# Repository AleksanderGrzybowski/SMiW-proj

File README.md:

# SMiW-proj
An ATmega16 based clock on steroids

This is DS1307 + ATmega based digital clock, made for Embedded Systems course. Developed on mega16 at the university (cause everyone were using mega8 for no reason), switched to mega8 later.
Includes multiplexing, I2C interfacing and buttons for setting time, brightness and other settings.

In the second version I remade it to work fully on a single 18650 battery (lasts for a week or so on a cheap cell extracted from a broken powerbank), with battery voltage monitoring. USB charger module and boost module (3.7 -> 5) are glued on the backside.

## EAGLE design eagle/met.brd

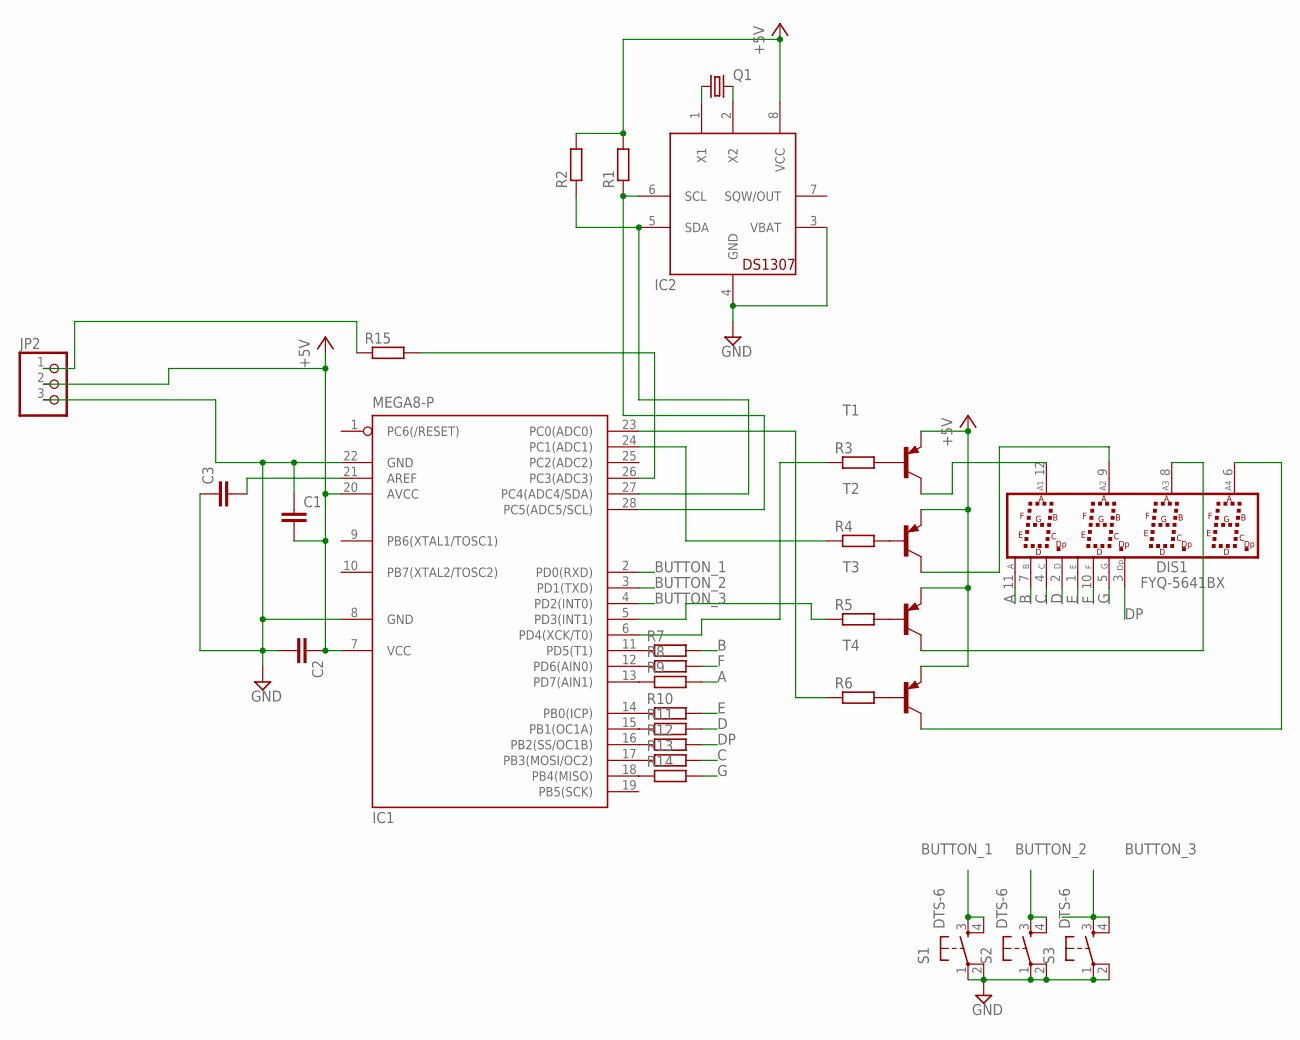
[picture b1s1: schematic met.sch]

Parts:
C1, C2, C3: C-EU025-024X044; C025-024X044
DIS1: FYQ-5641BX; FYQ5641
IC1: MEGA8-P; DIL28-3
IC2: DS1307; DIL08
JP2: PINHD-1X3; 1X03
Q1: CRYSTALTC26V; TC26V
R1, R2: R-EU_0207/2V; 0207/2V
R3, R4, R5, R6, R7, R8, R9, R10, R11, R12, R13, R14, R15: R-EU_0204/2V; 0204V
S1, S2, S3: DTS-6
T1, T2, T3, T4: BC327-PNP-TO92-EBC; TO92-EBC

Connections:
+5V: C1.2, C2.1, IC1.7 (VCC), IC1.20 (AVCC), IC2.8 (VCC), JP2.2, R1.2, R2.2, T1.E, T2.E, T3.E, T4.E
A: DIS1.11 (A), R9.2
B: DIS1.7 (B), R7.2
BUTTON_1: IC1.2 (PD0(RXD)), S1.3, S1.4
BUTTON_2: IC1.3 (PD1(TXD)), S2.3, S2.4
BUTTON_3: IC1.4 (PD2(INT0)), S3.3, S3.4
C: DIS1.4 (C), R13.2
D: DIS1.2 (D), R11.2
D2: DIS1.9 (A2), T2.C
D3: DIS1.8 (A3), T3.C
DOT: IC1.27 (PC4(ADC4/SDA)), IC2.5 (SDA), R2.1
DP: DIS1.3 (DP), R12.2
E: DIS1.1 (E), R10.2
F: DIS1.10 (F), R8.2
G: DIS1.5 (G), R14.2
GND: C1.1, C2.2, C3.1, IC1.8 (GND), IC1.22 (GND), IC2.3 (VBAT), IC2.4 (GND), JP2.3, S1.1, S1.2, S2.1, S2.2, S3.1, S3.2
unnamed: IC2.1 (X1), Q1.1
unnamed: IC2.2 (X2), Q1.2
unnamed: C3.2, IC1.21 (AREF)
unnamed: JP2.1, R15.1
unnamed: DIS1.6 (A4), T4.C
unnamed: IC1.28 (PC5(ADC5/SCL)), IC2.6 (SCL), R1.1
unnamed: IC1.23 (PC0(ADC0)), R6.1
unnamed: IC1.6 (PD4(XCK/T0)), R3.1
unnamed: R5.2, T3.B
unnamed: R3.2, T1.B
unnamed: R4.2, T2.B
unnamed: R6.2, T4.B
unnamed: IC1.24 (PC1(ADC1)), R4.1
unnamed: IC1.5 (PD3(INT1)), R5.1
unnamed: IC1.11 (PD5(T1)), R7.1
unnamed: IC1.12 (PD6(AIN0)), R8.1
unnamed: IC1.13 (PD7(AIN1)), R9.1
unnamed: IC1.14 (PB0(ICP)), R10.1
unnamed: IC1.15 (PB1(OC1A)), R11.1
unnamed: IC1.16 (PB2(SS/OC1B)), R12.1
unnamed: IC1.17 (PB3(MOSI/OC2)), R13.1
unnamed: DIS1.12 (A1), T1.C
unnamed: IC1.18 (PB4(MISO)), R14.1
unnamed: IC1.26 (PC3(ADC3)), R15.2

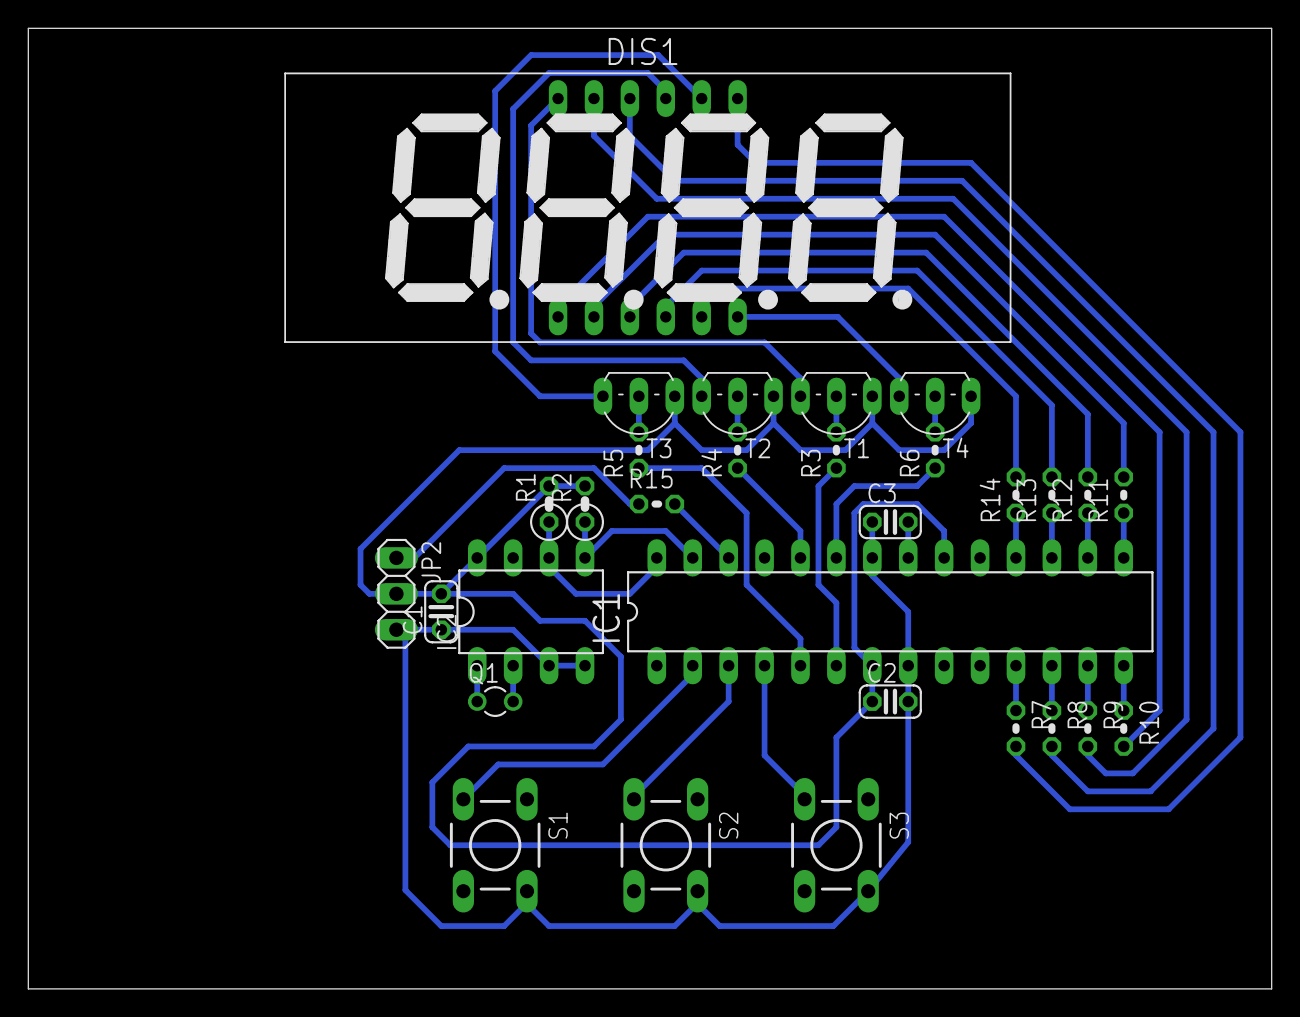
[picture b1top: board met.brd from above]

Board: 2 copper layers, 87.9 x 67.9 mm, 30 parts (0 on the bottom side), 40 nets.

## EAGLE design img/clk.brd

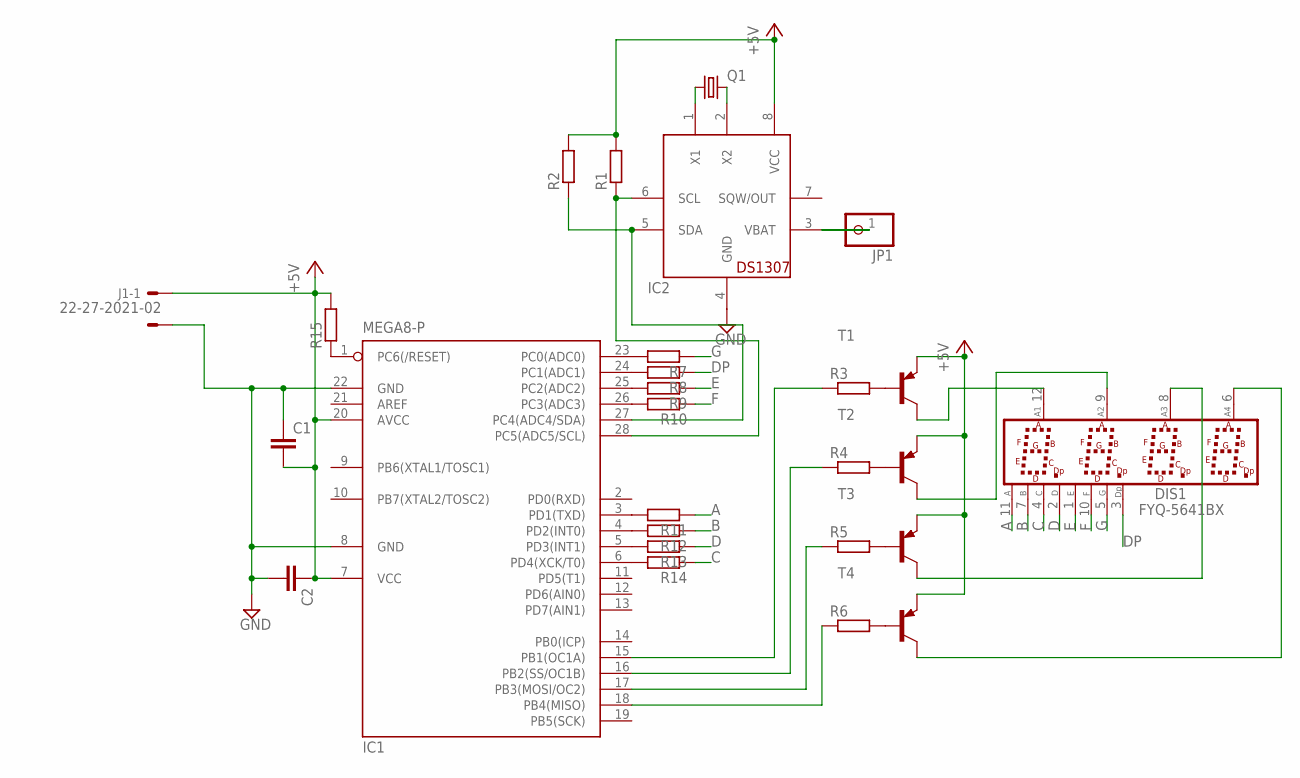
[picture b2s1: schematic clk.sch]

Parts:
C1, C2: C-EU025-024X044; C025-024X044
DIS1: FYQ-5641BX; FYQ5641
IC1: MEGA8-P; DIL28-3
IC2: DS1307; DIL08
J1: 22-27-2021-02; 6410-02
JP1: PINHD-1X1; 1X01
Q1: CRYSTALTC26V; TC26V
R1, R2, R7, R8, R9, R10, R11, R12, R13, R14: R-EU_0207/2V; 0207/2V
R3, R4, R5, R6, R15: R-EU_0204/2V; 0204V
T1, T2, T3, T4: BC327-PNP-TO92-EBC; TO92-EBC

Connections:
+5V: C1.2, C2.1, IC1.7 (VCC), IC1.20 (AVCC), IC2.8 (VCC), J1.1, R1.2, R2.2, R15.2, T1.E, T2.E, T3.E, T4.E
A: DIS1.11 (A), R11.1
B: DIS1.7 (B), R12.1
C: DIS1.4 (C), R14.1
D: DIS1.2 (D), R13.1
D2: DIS1.9 (A2), T2.C
D3: DIS1.8 (A3), T3.C
DOT: IC1.27 (PC4(ADC4/SDA)), IC2.5 (SDA), R2.1
DP: DIS1.3 (DP), R8.1
E: DIS1.1 (E), R9.1
F: DIS1.10 (F), R10.1
G: DIS1.5 (G), R7.1
GND: C1.1, C2.2, IC1.8 (GND), IC1.22 (GND), IC2.4 (GND), J1.2
unnamed: IC2.1 (X1), Q1.1
unnamed: IC2.2 (X2), Q1.2
unnamed: IC1.23 (PC0(ADC0)), R7.2
unnamed: IC1.24 (PC1(ADC1)), R8.2
unnamed: DIS1.6 (A4), T4.C
unnamed: IC1.28 (PC5(ADC5/SCL)), IC2.6 (SCL), R1.1
unnamed: IC2.3 (VBAT), JP1.1
unnamed: IC1.25 (PC2(ADC2)), R9.2
unnamed: R5.2, T3.B
unnamed: R3.2, T1.B
unnamed: R4.2, T2.B
unnamed: R6.2, T4.B
unnamed: IC1.1 (PC6(/RESET)), R15.1
unnamed: IC1.16 (PB2(SS/OC1B)), R4.1
unnamed: IC1.17 (PB3(MOSI/OC2)), R5.1
unnamed: IC1.18 (PB4(MISO)), R6.1
unnamed: IC1.26 (PC3(ADC3)), R10.2
unnamed: IC1.3 (PD1(TXD)), R11.2
unnamed: IC1.4 (PD2(INT0)), R12.2
unnamed: IC1.5 (PD3(INT1)), R13.2
unnamed: IC1.6 (PD4(XCK/T0)), R14.2
unnamed: IC1.15 (PB1(OC1A)), R3.1
unnamed: DIS1.12 (A1), T1.C

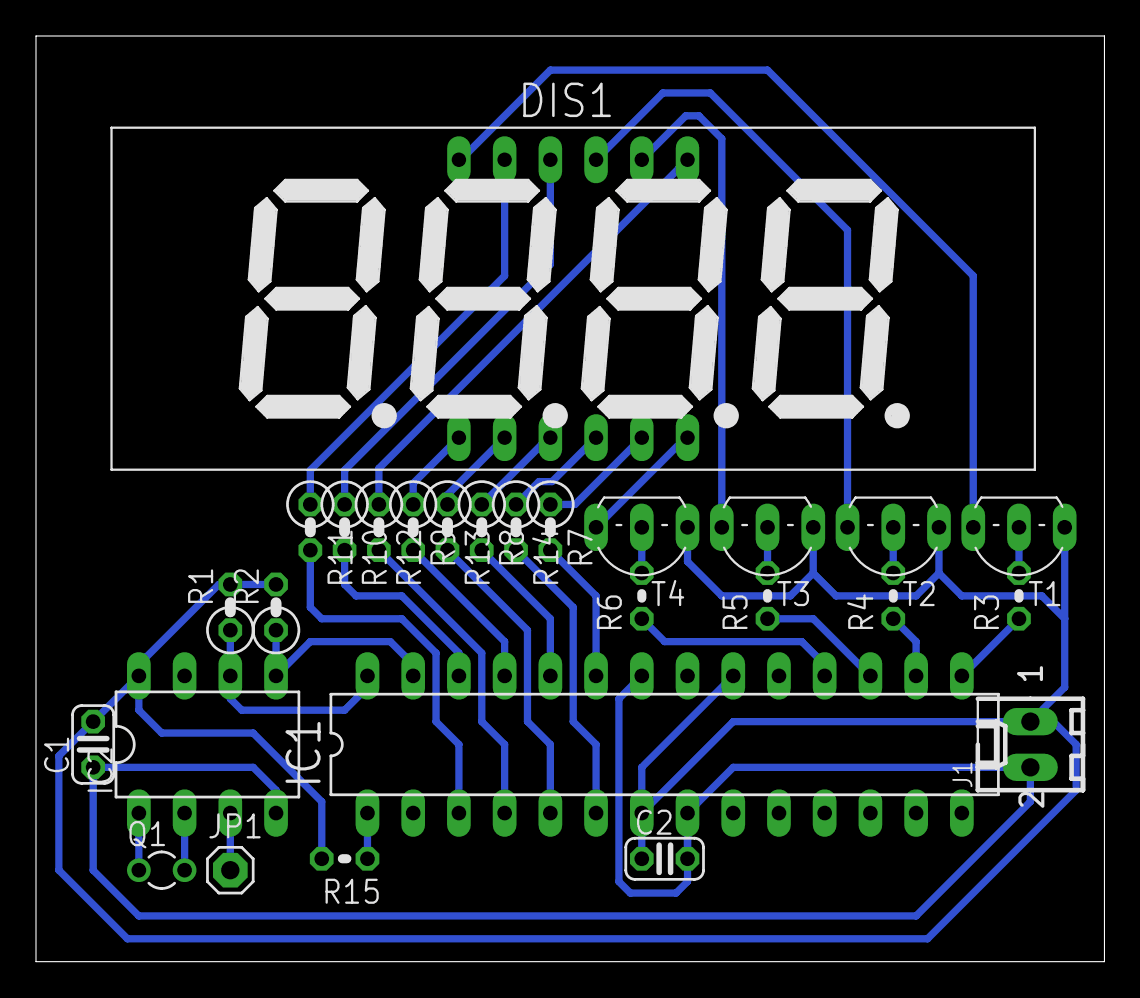
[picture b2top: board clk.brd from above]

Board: 2 copper layers, 59.4 x 51.4 mm, 27 parts (0 on the bottom side), 36 nets.

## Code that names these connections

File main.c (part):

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
/////////////////////////////////////////////////////

#define DOT 128
#define G 64
#define F 32
#define E 16
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    }

    /* prevent ghosting */
    PORTB |= (1 << PB0) | (1 << PB1) | (1 << PB2) | (1 << PB3) | (1 << PB4);
    PORTD |= (1 << PD5) | (1 << PD6) | (1 << PD7);

    PORTC |= (1 << PC0) | (1 << PC1);
    PORTD |= (1 << PD3) | (1 << PD4);

    /* turn on/off current digit, based on pwm current value */
    int real_brightness = is_night ? NIGHT_BRIGHTNESS : brightness;
    if (pwm_iter < real_brightness) {
        if (current_digit == 3) {
            PORTC &= ~(1 << PC0);
        }
        if (current_digit == 1) {
            PORTC &= ~(1 << PC1);
        }
        if (current_digit == 2) {
            PORTD &= ~(1 << PD3);
        }
        if (current_digit == 0) {
            PORTD &= ~(1 << PD4);
        }
    } 

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    uint8_t value = ~tab[display[current_digit]];

    if (value & 1) {
        PORTD |= (1 << PD7);
    } else {
        PORTD &= ~(1 << PD7);
    }
    if (value & 2) {
        PORTD |= (1 << PD5);
    } else {
        PORTD &= ~(1 << PD5);
    }
    if (value & 4) {
        PORTB |= (1 << PB3);
    } else {
        PORTB &= ~(1 << PB3);
    }
    if (value & 8) {
        PORTB |= (1 << PB1);
    } else {
        PORTB &= ~(1 << PB1);
    }
    if (value & 16) {
        PORTB |= (1 << PB0);
    } else {
        PORTB &= ~(1 << PB0);
    }
    if (value & 32) {
        PORTD |= (1 << PD6);
    } else {
        PORTD &= ~(1 << PD6);
    }
    if (value & 64) {
        PORTB |= (1 << PB4);
    } else {
        PORTB &= ~(1 << PB4);
    }
    if (current_digit == 1 && dot_on) {
        PORTB &= ~(1 << PB2);
    } else {
        PORTB |= (1 << PB2);
    }
}

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    sei();

    /* display outputs */
    DDRC |= (1 << PC0) | (1 << PC1);
    DDRD |= (1 << PD3) | (1 << PD4);
    DDRB |= (1 << PB0) | (1 << PB1) | (1 << PB2) | (1 << PB3) | (1 << PB4);
    DDRD |= (1 << PD5) | (1 << PD6) | (1 << PD7);

    /* buttons inputs */
    CONF_BUTTON_SETTIME_DDR &= ~_BV(CONF_BUTTON_SETTIME_NUM);
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

    // ADC input
    DDRC &= ~(1 << PC3);
    PORTC &= ~(1 << PC3);
    adc_init();

    /* start RTC and check if it ticks, it might be stuck on cold start, 
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
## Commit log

2014-11-12 Initial: add everyting what I have
2014-11-13 Simple soft PWM
2014-11-13 Don't display leading 0
2014-11-13 Replaced old ds18b20 lib with working one, lol
2014-11-13 Moved 7seg abcdefgD to PORTD, so we can use ADC later
2014-11-13 Added buttons to set current time
2014-11-13 'SET' text displayed when in that mode
2014-11-13 Function to display single 4-digit number (debug)
2014-11-13 Added phototransistor and working ADC displaying
2014-11-19 Buttons to show temp/light, no auto
2014-11-20 'INIT' displaying on uC bootup
2014-11-20 Add stub implementation of light-sensed pwm
2014-11-20 Delay after setting noon, would cause inf. loop
2014-11-20 Set all ports to inputs at bootup, ref to macros
2014-11-24 Refactored set_time() so alarm can be set the same way
2014-11-24 Added alarm on/off
2014-11-24 Added jumper to let ignore phototr readings
2014-11-24 Add temp display jumper
2014-11-24 Some ref, uint8_t vals and pointers
2014-11-25 In input mode digits blink
2014-11-25 Better handling of blinking while delaying
2014-11-25 Minor ref
2014-11-26 Alarm of is '0', on is '1' - added buzzer so needed to change
2014-11-26 Read temperature less often
2014-11-28 Remove unnecessary delay_us
2014-12-01 Better main, simpler config
2014-12-06 Remove "INIT" on start, turn off pnp-s while switching digits
2014-12-06 Remove unneeded files
2014-12-06 Comments
2015-06-29 Removed unneeded features (alarm/buzzer/photo/adc)
2015-07-05 Finish port to ATmega8
2015-07-05 Remove temperature reading
2015-07-07 Fixed ghosting (took me 2 hours to find out lol)
2015-07-27 User can change brightness
2015-07-27 Finished project
2015-08-17 Persist brightness in nonvolatile memory
2016-12-15 Makefile, small changes
2016-12-18 Adjust code to the new board layout
2017-01-17 Final board and photos
2017-07-27 Working 7-segment display
2017-07-27 Port to ATmega8, hacking around strange issue
2017-07-27 FML fix ghosting finally
2017-07-27 Finally working as intended
2017-07-28 Measuring and selecting threshold voltage
2017-07-28 Add battery monitoring
2017-07-28 Typo
2017-07-28 Do not store brightness in EEPROM
2017-07-28 12 PWM levels
2017-07-28 Show 'low battery' for longer time
2017-07-28 General refactor
2017-09-09 Finished and tested version 2
2017-11-18 Back up Eagle files
